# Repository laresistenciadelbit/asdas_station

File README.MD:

# (A)rduino (S)im (D)ata (A)cquisition (S)ystem

[FULL DOCUMENTATION (SPANISH)](https://github.com/laresistenciadelbit/varios/raw/master/ASDAS_PUBLIC_LITE.PDF)

## SPANISH

Arduino Sim Data Acquisition System es un proyecto que cubre toda la parte de
adquisición de datos de sensores desde el circuito físico, a la transmisión de los datos,su almacenaje, y su visualización en tiempo real desde un navegador Web.

Un dispositivo estación hecho con Arduino envía peticiones JSON HTTP POST al servidor.

Este repositorio de Github almacena la parte del dispositivo estación.

La parte del servidor la puedes encontrar en:
[https://github.com/laresistenciadelbit/asdas](https://github.com/laresistenciadelbit/asdas)

#### ESTACIÓN ASDAS

La estación cuenta con un módulo SIM para mandar los datos por la red móvil, un microcontrolador (Arduino Pro Micro versión 3.3V), un lector de tarjetas Micro SD para almacenar los datos que no se hubiesen podido enviar por falta de señal, y un sistema de autonomía con batería, panel solar y un conversor de voltaje que distribuye la energía y carga la batería. También se le añadirán tantos sensores como se desee (hasta el límite de entradas del microcontrolador)

#### CARPETAS DEL PROYECTO

- arduino_sketch

>Aquí encontrarás el sketch para compilarlo en arduino. 

>He tomado la librería oficial de sim808 y la he modificado para hacerla compatible con más módulos y he añadido alguna función.
Es necesario usarla para que funcione el sketch:

[https://github.com/laresistenciadelbit/sim8xx](https://github.com/laresistenciadelbit/sim8xx)

>###### Se instala como el resto de librerías: Se pega su contenido en la carpeta libraries de la carpeta Arduino (o bien la que aparece en mis documentos o bien en la de instalación del programa)

.
- kicad_project

>Aquí encontrarás los esquemas del prototipo de pcb y circuito en formato kicad

.

- blender

>Aquí encontrarás los modelos 3d que forman la estructura para el prototipo

.

___
.
## ENGLISH

ASDAS is a project which covers all the data acquisition part of sensors starting from the physical circuit followed by the data transmission, its storage and visualization in real time from a Web Browser.

A station device made with Arduino send HTTP POST JSON messages to the server.

This Github project is the station part.

The server Github can be accessed from:

[https://github.com/laresistenciadelbit/asdas](https://github.com/laresistenciadelbit/asdas)

#### ASDAS STATION

The station counts with a Sim module for sending data to the server throught the mobile network, a microcontroller (Arduino Pro Micro 3.3V), a micro SD reader for storing the data that wouldn't be delivered to the server by signal fail, and an autonomous energy system with battery, solar panel and voltage conversor which distributes energy and charges the battery. Also ther will be added so many sensors as is wished (until the microcontroller I/O ports limit)

#### PROJECT FOLDERS

- arduino_sketch

>Here you can get the sketch for compiling in Arduino

> I've took the official sim808 library and I've modified it for making compatible with more Sim modules and I've also added some function.
The library must be used with this sketch to work:
[https://github.com/laresistenciadelbit/sim8xx](https://github.com/laresistenciadelbit/sim8xx)

>###### The install process for the library is the same like other libraries: Just paste its content in the "libraries" folder from the install directory or "my documents/Arduino" directory.

.
- kicad_project

>Here you can get the pcb and circuit schemas in KiCad format.

.

- blender

>Here you can get the 3d models of the created structure for the prototype

.

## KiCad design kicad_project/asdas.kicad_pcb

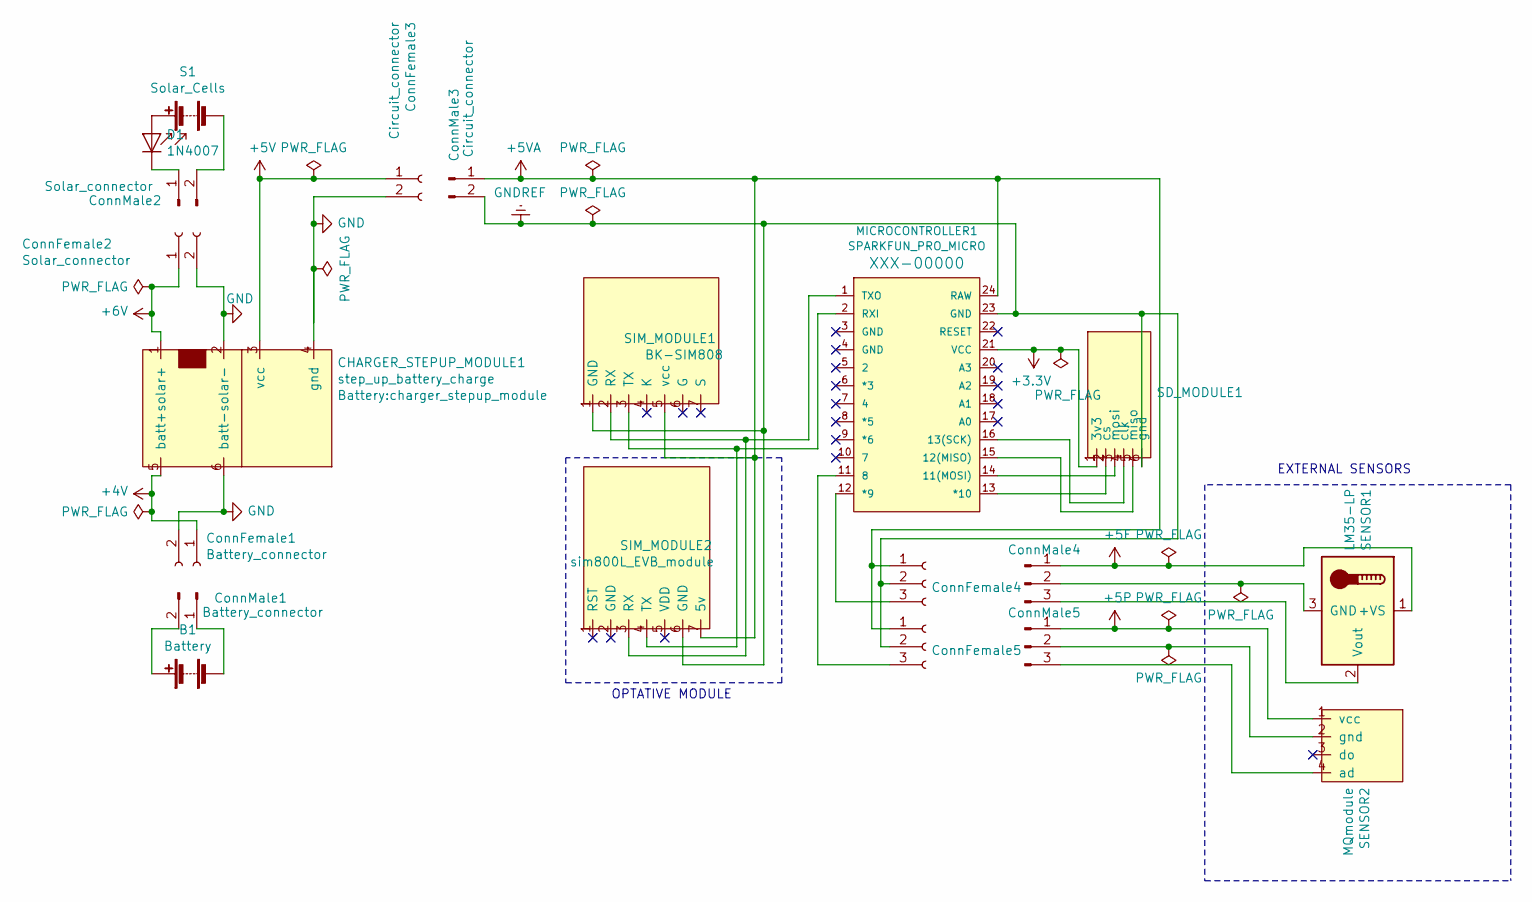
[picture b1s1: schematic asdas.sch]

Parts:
B1: Battery; battery_523450
CHARGER_STEPUP_MODULE1: step_up_battery_charge; charger_stepup_module
ConnFemale1: Battery_connector; JST_EH_B2B-EH-A_1x02_P2.50mm_Vertical
ConnFemale2: Solar_connector; JST_EH_B2B-EH-A_1x02_P2.50mm_Vertical
ConnFemale3: Circuit_connector; JST_EH_B2B-EH-A_1x02_P2.50mm_Vertical
ConnFemale4: Sensor1_connector; JST_EH_B3B-EH-A_1x03_P2.50mm_Vertical
ConnFemale5: Sensor2_connector; JST_EH_B3B-EH-A_1x03_P2.50mm_Vertical
ConnMale1: Battery_connector; JST_EH_B2B-EH-A_1x02_P2.50mm_Vertical
ConnMale2: Solar_connector; JST_EH_B2B-EH-A_1x02_P2.50mm_Vertical
ConnMale3: Circuit_connector; JST_EH_B2B-EH-A_1x02_P2.50mm_Vertical
ConnMale4: Sensor1_connector; JST_EH_B3B-EH-A_1x03_P2.50mm_Vertical
ConnMale5: Sensor2_connector; JST_EH_B3B-EH-A_1x03_P2.50mm_Vertical
D1: 1N4007; D_DO-41_SOD81_P10.16mm_Horizontal
MICROCONTROLLER1: SPARKFUN_PRO_MICRO
S1: Solar_Cells; solar_cell
SD_MODULE1: sd_reader_2
SENSOR1: LM35-LP; lm35
SENSOR2: MQmodule
SIM_MODULE1: BK-SIM808
SIM_MODULE2: sim800L_EVB_module; sim800L_EVB_module(fixedsize)

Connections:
+3V3: MICROCONTROLLER1.21 (VCC), SD_MODULE1.1 (3v3)
+4V: CHARGER_STEPUP_MODULE1.5 (batt+), ConnFemale1.1
+5F: ConnMale4.1, SENSOR1.1 (+VS)
+5P: ConnMale5.1, SENSOR2.1 (vcc)
+5V: CHARGER_STEPUP_MODULE1.3 (vcc), ConnFemale3.1
+5VA: ConnFemale4.1, ConnFemale5.1, ConnMale3.1, MICROCONTROLLER1.24 (RAW), SIM_MODULE1.5 (vcc), SIM_MODULE2.7 (5v)
+6V: CHARGER_STEPUP_MODULE1.1 (solar+), ConnFemale2.1
GND: CHARGER_STEPUP_MODULE1.2 (solar-), CHARGER_STEPUP_MODULE1.4 (gnd), CHARGER_STEPUP_MODULE1.6 (batt-), ConnFemale1.2, ConnFemale2.2, ConnFemale3.2
GNDREF: ConnFemale4.2, ConnFemale5.2, ConnMale3.2, MICROCONTROLLER1.23 (GND), SD_MODULE1.6 (gnd), SIM_MODULE1.1 (GND), SIM_MODULE2.6 (GND)
unnamed: B1.1 (+), ConnMale1.2
unnamed: B1.2 (-), ConnMale1.1
unnamed: ConnFemale4.3, MICROCONTROLLER1.12 (*9)
unnamed: ConnFemale5.3, MICROCONTROLLER1.11 (8)
unnamed: ConnMale2.1, D1.1 (K)
unnamed: ConnMale2.2, S1.2 (-)
unnamed: ConnMale4.2, SENSOR1.3 (GND)
unnamed: ConnMale4.3, SENSOR1.2 (Vout)
unnamed: ConnMale5.2, SENSOR2.2 (gnd)
unnamed: ConnMale5.3, SENSOR2.4 (ad)
unnamed: D1.2 (A), S1.1 (+)
unnamed: MICROCONTROLLER1.1 (TXO), SIM_MODULE1.2 (RX), SIM_MODULE2.3 (RX)
unnamed: MICROCONTROLLER1.2 (RXI), SIM_MODULE1.3 (TX), SIM_MODULE2.4 (TX)
unnamed: MICROCONTROLLER1.13 (*10), SD_MODULE1.2 (cs)
unnamed: MICROCONTROLLER1.14 (11(MOSI)), SD_MODULE1.3 (mosi)
unnamed: MICROCONTROLLER1.15 (12(MISO)), SD_MODULE1.5 (miso)
unnamed: MICROCONTROLLER1.16 (13(SCK)), SD_MODULE1.4 (clk)

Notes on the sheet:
EXTERNAL SENSORS
OPTATIVE MODULE

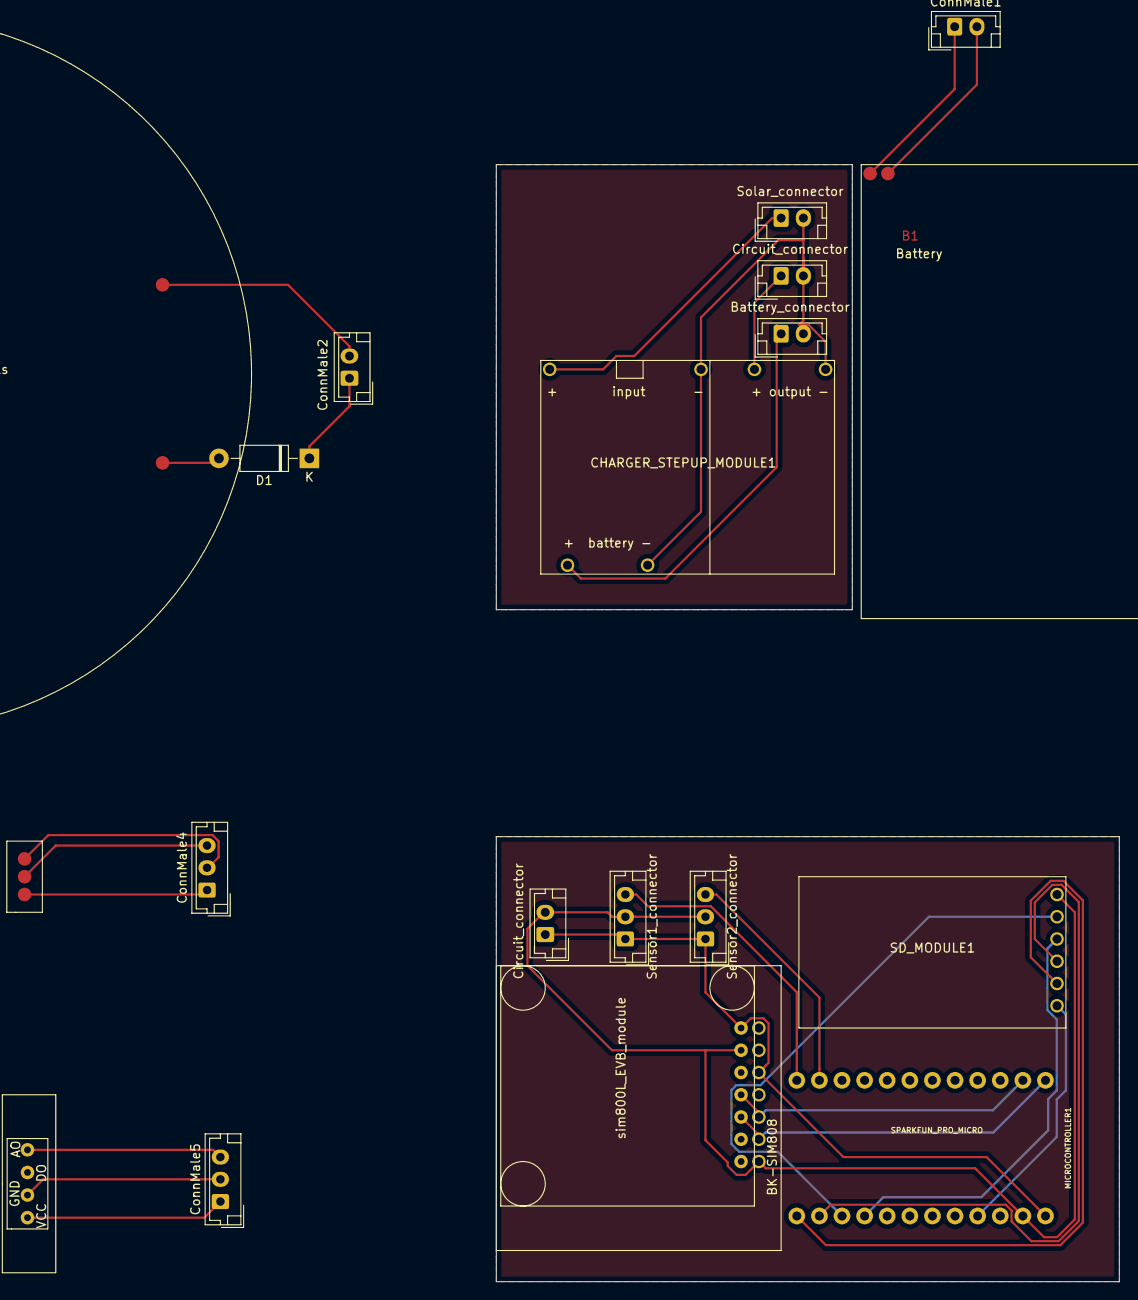
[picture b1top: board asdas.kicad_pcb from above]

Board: 2 copper layers, 20 parts (0 on the bottom side), 26 nets.

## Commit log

2020-08-17 sim808 gps send with sim by POST
2020-08-24 sim808+sim800l
2020-08-31 library change to TinyGSM which includes all sim8xx models
2020-10-13 transform into class (even if module is not still working)
2020-10-21 transform code for sim808 library type instead of tinygsm
2020-10-27 clock + http post from url encode to json
2020-10-28 compiles fine. adding sd write
2020-10-30 compiles fine. addED sd write.
2020-12-08 status/gps in different data post
2020-12-11 "password" sent as GET in the http POST to be identified by the server
2021-01-20 restructuring loop() code order
2021-01-24 combine save_data_in_sd and save_aditinal_data_in_sd into one function
2021-01-30 -fixed strcpy & strcat -fixed apn user & pass NULL pointer detection -realized Serial1 is on TX0 & RXI -raised timeout of AT commands from Sim8xx library -clock output response (fixed in Sim8xx libra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
2021-02-03 -fixed status counter not raising due to pointer -modified and added the use of a function in library sim8xx to read gprs status -status http petitions were malformed
2021-02-04 -improved delay managemente (now using millis()) -fixed sd reading lines
2021-02-17 -fixed network registration status if not working properly -sketch exceeded available space when compiling with: USE_GPS 1 >shared buffer between gps and http parameters >convert some int into uint8_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
2021-03-23 - added readme, circuit sketch, and blender model
2021-03-23 README.MD fix
2021-04-07 readme update
2021-04-28 pdf updated
